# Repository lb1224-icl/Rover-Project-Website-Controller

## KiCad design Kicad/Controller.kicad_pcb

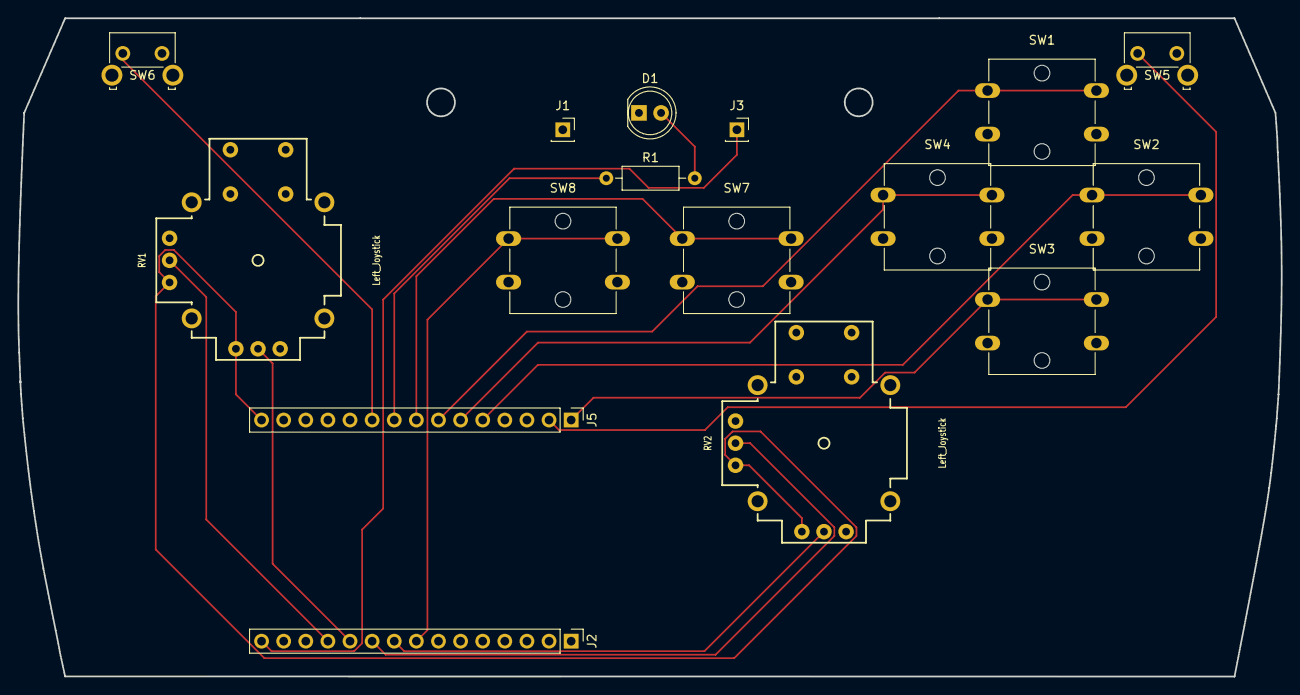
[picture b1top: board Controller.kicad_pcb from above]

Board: 2 copper layers, 145.1 x 75.6 mm, 16 parts (0 on the bottom side), 17 nets.

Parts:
D1: LED; LED_D5.0mm
J1: GND from TP4056; PinSocket_1x01_P2.54mm_Vertical
J2, J5: Conn_01x15_Pin; PinHeader_1x15_P2.54mm_Vertical
J3: VIN from TP4056; PinSocket_1x01_P2.54mm_Vertical
R1: R; R_Axial_DIN0207_L6.3mm_D2.5mm_P10.16mm_Horizontal
RV1, RV2: Left_Joystick; Joystick
SW1: Up; SW_SPST_Omron_B3F-40xx
SW2: Right; SW_SPST_Omron_B3F-40xx
SW3: Down; SW_SPST_Omron_B3F-40xx
SW4: Left; SW_SPST_Omron_B3F-40xx
SW5: Right_Shoulder; SW_SPST_Omron_B3F-315x_Angled
SW6: Left_Shoulder; SW_SPST_Omron_B3F-315x_Angled
SW7: Wifi; SW_SPST_Omron_B3F-40xx
SW8: Power; SW_SPST_Omron_B3F-40xx

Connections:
/3V3: J5.15, RV1.3, RV1.4, RV2.3, RV2.4
/D5: J5.8, SW7.1
/D12: J2.12, RV1.2
/D14: J2.11, RV1.5
/D16: J5.10, SW6.1
/D17: J5.9, R1.1
/D18: J5.7, SW1.1
/D19: J5.6, SW4.1
/D21: J5.5, SW2.1
/D22: J5.2, SW5.1
/D23: J5.1, SW3.1
/D25: J2.8, SW8.1
/D26: J2.9, RV2.5
/D27: J2.10, RV2.2
/GND: D1.1 (K), J1.1, J2.14, J5.14, RV1.1, RV1.6, RV2.1, RV2.6, SW1.2, SW2.2, SW3.2, SW4.2, SW5.2, SW6.2, SW7.2, SW8.2
/VIN: J2.15, J3.1
unnamed: D1.2 (A), R1.2

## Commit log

2025-09-09 Added Controller files
    Added Controller files including 3D models, PCB and KiCad files
2025-09-09 Added controller code
